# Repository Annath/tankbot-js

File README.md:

# tankbot-js
Tankbot rewrite in node.js using Zetta for the API and bonescript for HW interaction

#### TODO
* Add simple static device that just returns the URL for the camera, as a way for clients to retrieve the camera feed

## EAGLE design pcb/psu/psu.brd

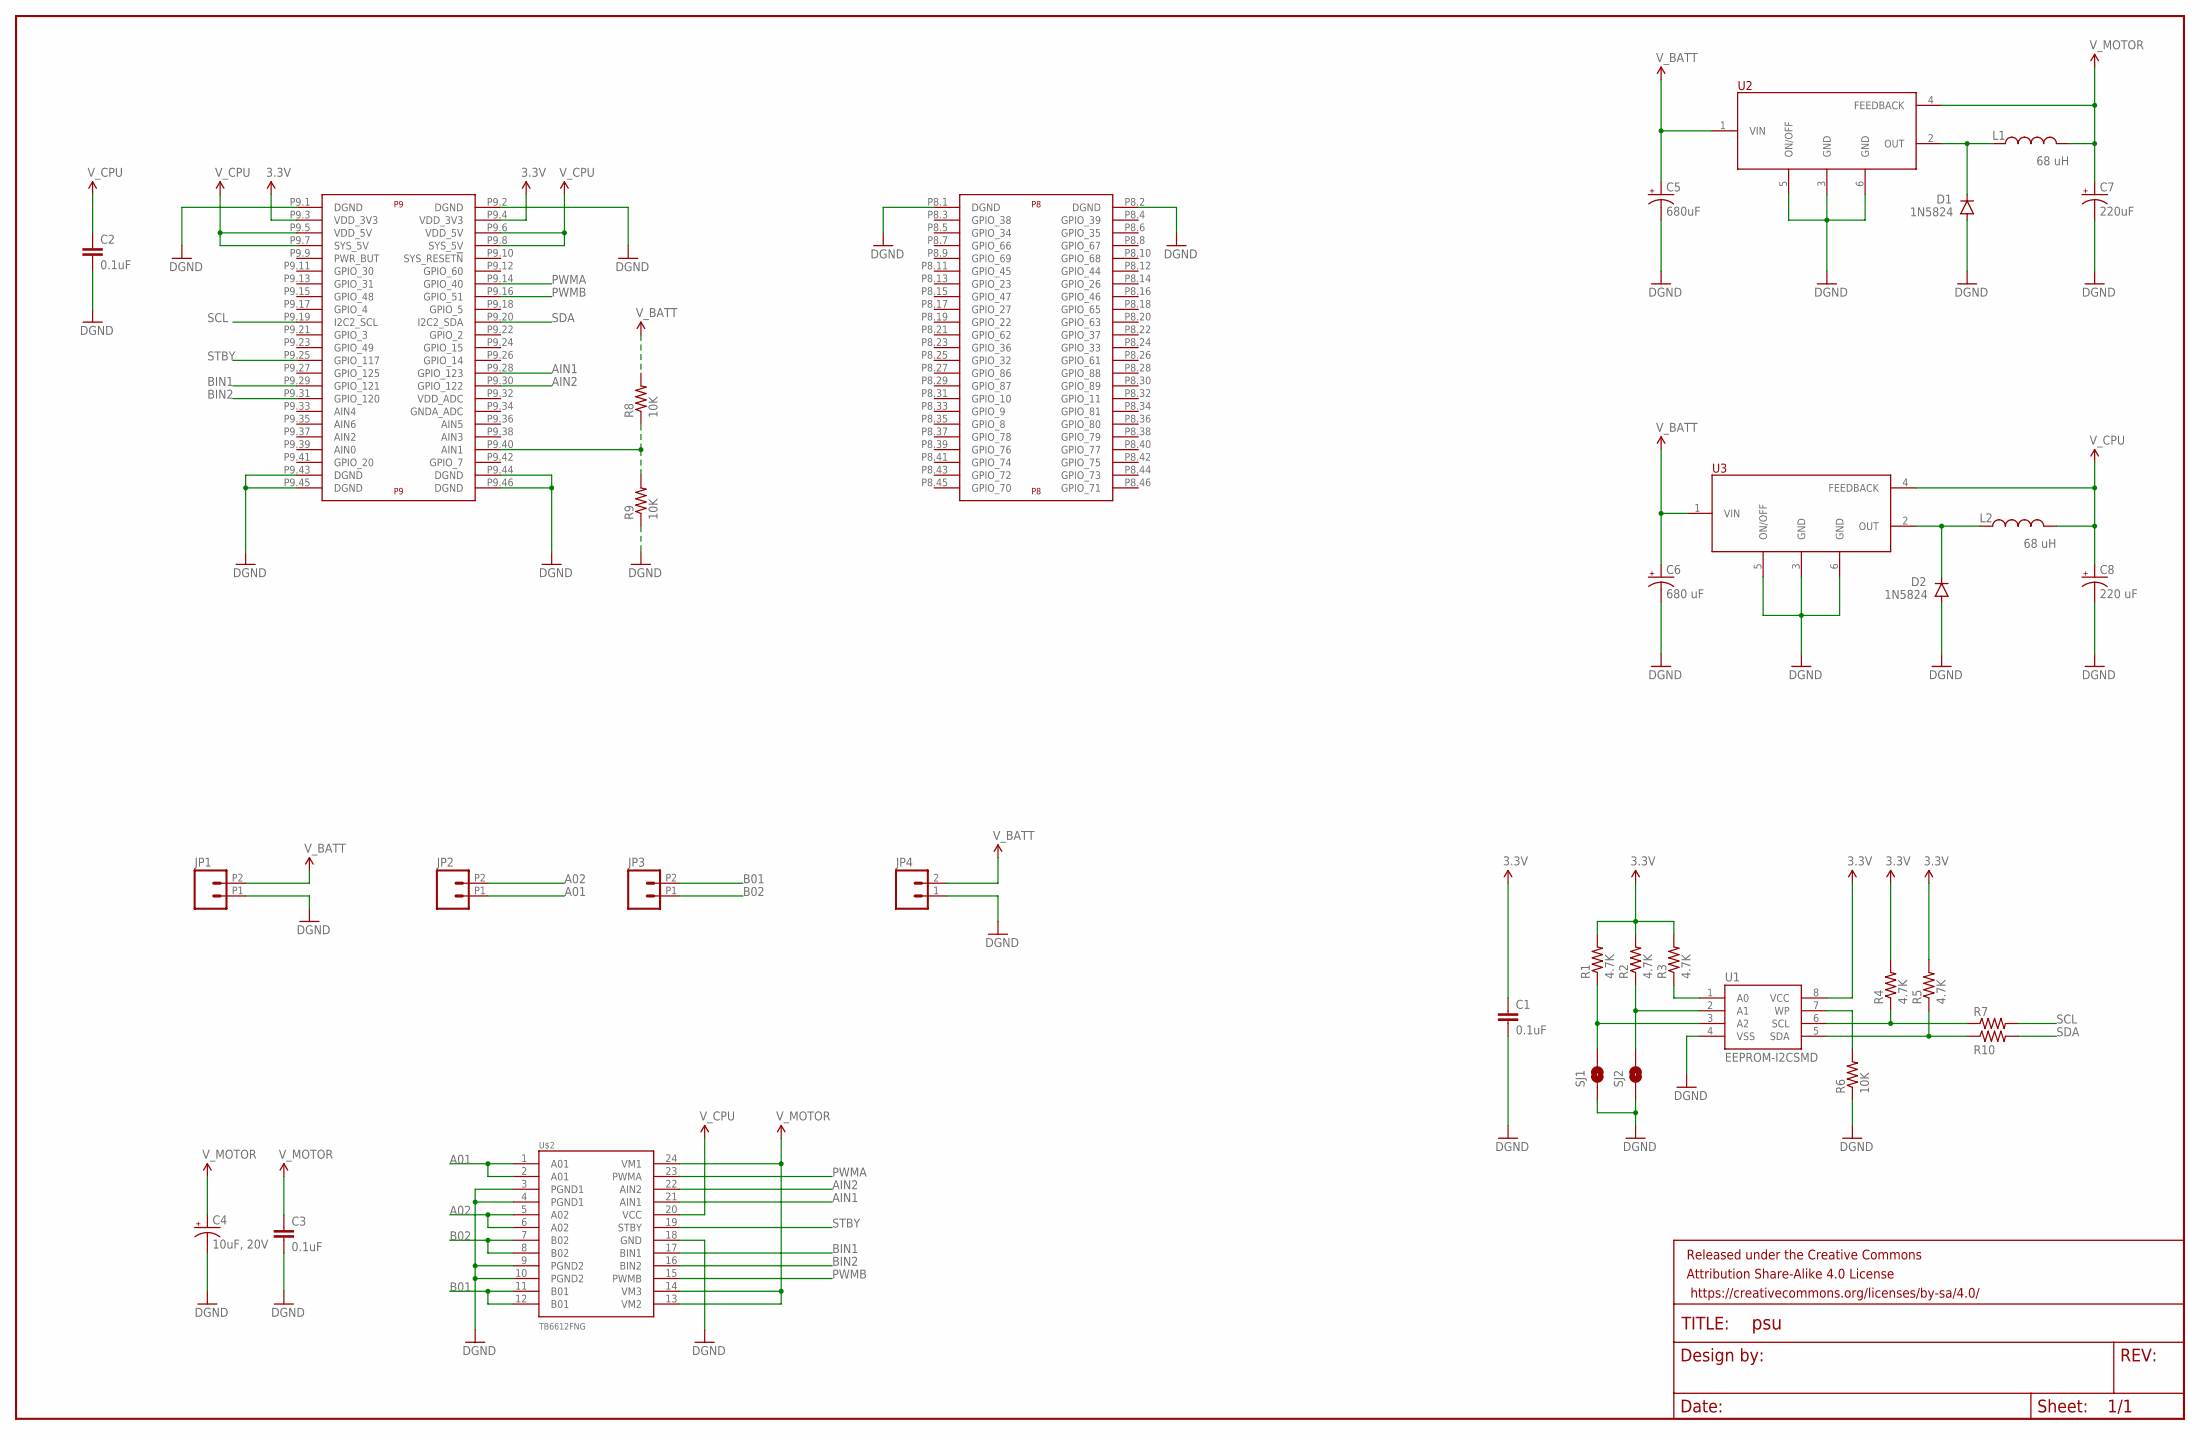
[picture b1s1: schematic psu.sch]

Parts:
C1, C2, C3: 0.1uF; 0603-CAP
C4: 10uF, 20V; CPOL-RADIAL-10UF-25V-KIT
C5: 680uF; CPOL-RADIAL-10UF-25V
C6: 680 uF; CPOL-RADIAL-10UF-25V
C7: 220uF; CPOL-RADIAL-10UF-25V
C8: 220 uF; CPOL-RADIAL-10UF-25V
D1, D2: 1N5824; DIODE-1N4001
FRAME2: FRAME-LEDGER; CREATIVE_COMMONS
JP1, JP2, JP3: M022.54MM_SCREWTERM; 1X02_2.54_SCREWTERM
JP4: M023.5MM; SCREWTERMINAL-3.5MM-2
L1, L2: 68 uH; 0603
R1, R2, R3, R4, R5: 4.7K; 0603-RES
R6, R8, R9: 10K; 0603-RES
R7, R10: 0; 0603-RES
SJ1, SJ2: JUMPER-PAD-2-NO; PAD-JUMPER-2-NO_NO_SILK
U1: EEPROM-I2CSMD; SO08
U2, U3: LM2596; TO-263
U$1: BEAGLE_BONE_BLACK_CAPE
U$2: TB6612FNG; SSOP24

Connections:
3.3V: C1.1, R1.2, R2.2, R3.2, R4.2, R5.2, U1.8 (VCC), U$1.P9.3 (VDD_3V3), U$1.P9.4 (VDD_3V3)
A01: JP2.P1 (1), U$2.1 (A01), U$2.2 (A01)
A02: JP2.P2 (2), U$2.5 (A02), U$2.6 (A02)
AIN1: U$1.P9.28 (GPIO_123), U$2.21 (AIN1)
AIN2: U$1.P9.30 (GPIO_122), U$2.22 (AIN2)
B01: JP3.P2 (2), U$2.11 (B01), U$2.12 (B01)
B02: JP3.P1 (1), U$2.7 (B02), U$2.8 (B02)
BIN1: U$1.P9.29 (GPIO_121), U$2.17 (BIN1)
BIN2: U$1.P9.31 (GPIO_120), U$2.16 (BIN2)
GND: C1.2, C2.2, C3.2, C4.2 (-), C5.2 (-), C6.2 (-), C7.2 (-), C8.2 (-), D1.A, D2.A, JP1.P1 (1), JP4.1, R6.1, R9.1, SJ1.1, SJ2.1, U1.4 (VSS), U2.3 (GND), U2.5 (ON/OFF), U2.6 (GND), U3.3 (GND), U3.5 (ON/OFF), U3.6 (GND), U$1.P8.1 (DGND), U$1.P8.2 (DGND), U$1.P9.1 (DGND), U$1.P9.2 (DGND), U$1.P9.43 (DGND), U$1.P9.44 (DGND), U$1.P9.45 (DGND), U$1.P9.46 (DGND), U$2.3 (PGND1), U$2.4 (PGND1), U$2.9 (PGND2), U$2.10 (PGND2), U$2.18 (GND)
unnamed: R3.1, U1.1 (A0)
unnamed: R2.1, SJ2.2, U1.2 (A1)
unnamed: R1.1, SJ1.2, U1.3 (A2)
unnamed: R8.1, R9.2, U$1.P9.40 (AIN1)
unnamed: R6.2, U1.7 (WP)
unnamed: D1.C, L1.1, U2.2 (OUT)
unnamed: D2.C, L2.1, U3.2 (OUT)
PWMA: U$1.P9.14 (GPIO_40), U$2.23 (PWMA)
PWMB: U$1.P9.16 (GPIO_51), U$2.15 (PWMB)
SCL: R7.2, U$1.P9.19 (I2C2_SCL)
SCL_PRE: R4.1, R7.1, U1.6 (SCL)
SDA: R10.2, U$1.P9.20 (I2C2_SDA)
SDA_PRE: R5.1, R10.1, U1.5 (SDA)
STBY: U$1.P9.25 (GPIO_117), U$2.19 (STBY)
V_BATT: C5.1 (+), C6.1 (+), JP1.P2 (2), JP4.2, R8.2, U2.1 (VIN), U3.1 (VIN)
V_CPU: C2.1, C8.1 (+), L2.2, U3.4 (FEEDBACK), U$1.P9.5 (VDD_5V), U$1.P9.6 (VDD_5V), U$1.P9.7 (SYS_5V), U$1.P9.8 (SYS_5V), U$2.20 (VCC)
V_MOTOR: C3.1, C4.1 (+), C7.1 (+), L1.2, U2.4 (FEEDBACK), U$2.13 (VM2), U$2.14 (VM3), U$2.24 (VM1)

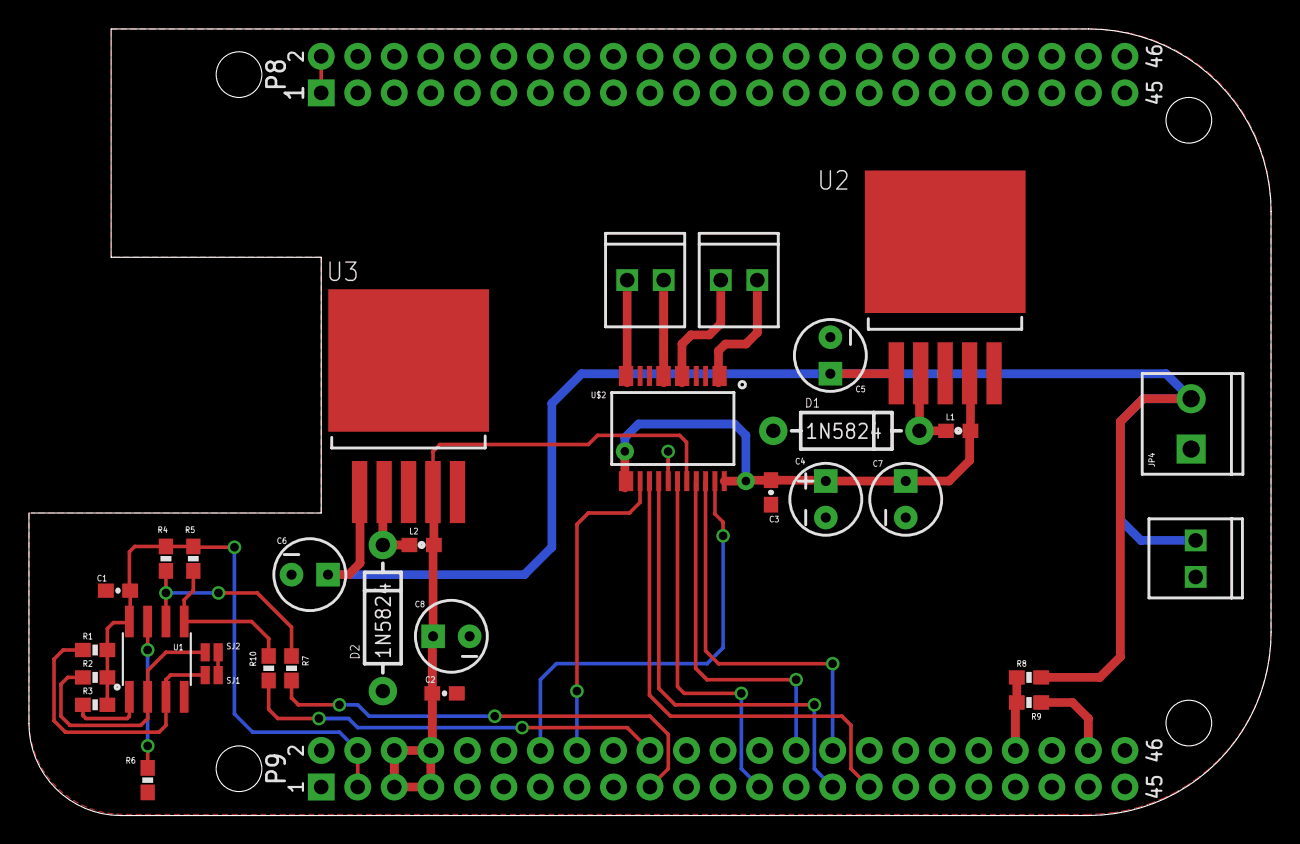
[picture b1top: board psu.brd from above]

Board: 2 copper layers, 86.4 x 54.7 mm, 34 parts (0 on the bottom side), 27 nets.

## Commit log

2015-01-19 Added npm info
2015-01-19 Added zetta dep to node setup
2015-01-19 Added empty server.js
2015-01-19 Added gitignore
2015-01-20 Added blank file for the motor driver
2015-01-20 Added most of the motor code, all untested so far
2015-01-20 Changed tabs to spaces
2015-01-21 Renamed driver js file
2015-01-21 Added index file
2015-01-21 Renamed driver file
2015-01-21 Added index file contents
2015-01-21 Added project file and ignore file
2015-01-21 Added basic server code
2015-01-21 Fixed minor bugs in server and added needed deps to package
2015-01-21 Tweaked servert to be even simpler
2015-01-21 Added a debug print and fixed some bugs in motor driver
2015-01-21 Fixed missing cb reference in the motor driver
2015-01-22 Fixed abs call
2015-01-22 Installed new bonescript package
2015-01-22 Changed motor driver to use octalbonescript
2015-01-22 Reverted to normal bonescript
2015-01-22 Fixed several bugs in the motor driver
2015-01-22 Fixed some issues in server, added second motor, and switched over to using autoscout
2015-01-22 Added battery measurement driver
2015-01-22 Added battery monitor to server
2015-01-22 Updated readme somwhat
2015-01-22 Removed octalbonescript from package
2015-01-30 Added corrected percentage calculation
2015-01-30 Added battery to server.js
2015-02-04 Changed battery module to use config array because of weird argument issue
2015-03-06 Added inversion control to zetta
2015-03-06 Removed unnecessary argument from inversion control
2015-03-06 Removed some debug statements from the battery driver
2015-03-07 Commented out more annoying prints and changed server name
2015-03-08 Added the beginnings of the simple controller app, which can currently read but not control
2015-12-18 Added adafruit eagle libs
2015-12-18 Added blank files for PSU board
2016-02-14 Updated board and layout, and updated gitignore
2016-02-14 Added cad libraries
2016-02-14 Fixed board outline
2016-02-14 Added OSH Park CAM file
2016-02-14 Restructured eagle files and folders
2016-03-16 Updated board layout with ground pours
2016-03-16 Added some datasheets to the repo
2016-03-16 Fixed via tenting
2016-03-16 Fixed one trace path to be a little more sane
2016-03-16 Changed via stop limit so that vias are covered
2016-03-19 Updated board layout and changed deans connector to screw terminal
2016-03-19 Lots of routing tweaks
2016-03-19 Filled pours
2017-03-01 Updated zetta package versions
2017-03-01 Updated gitignore

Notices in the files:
parts and their libraries:
SparkFun-DigitalIC: Licensing: Creative Commons ShareAlike 4.0 International - https://creativecommons.org/licenses/by-sa/4.0
SparkFun-Aesthetics: Released under the Creative Commons Attribution Share-Alike 4.0 License
SparkFun-Aesthetics: https://creativecommons.org/licenses/by-sa/4.0
